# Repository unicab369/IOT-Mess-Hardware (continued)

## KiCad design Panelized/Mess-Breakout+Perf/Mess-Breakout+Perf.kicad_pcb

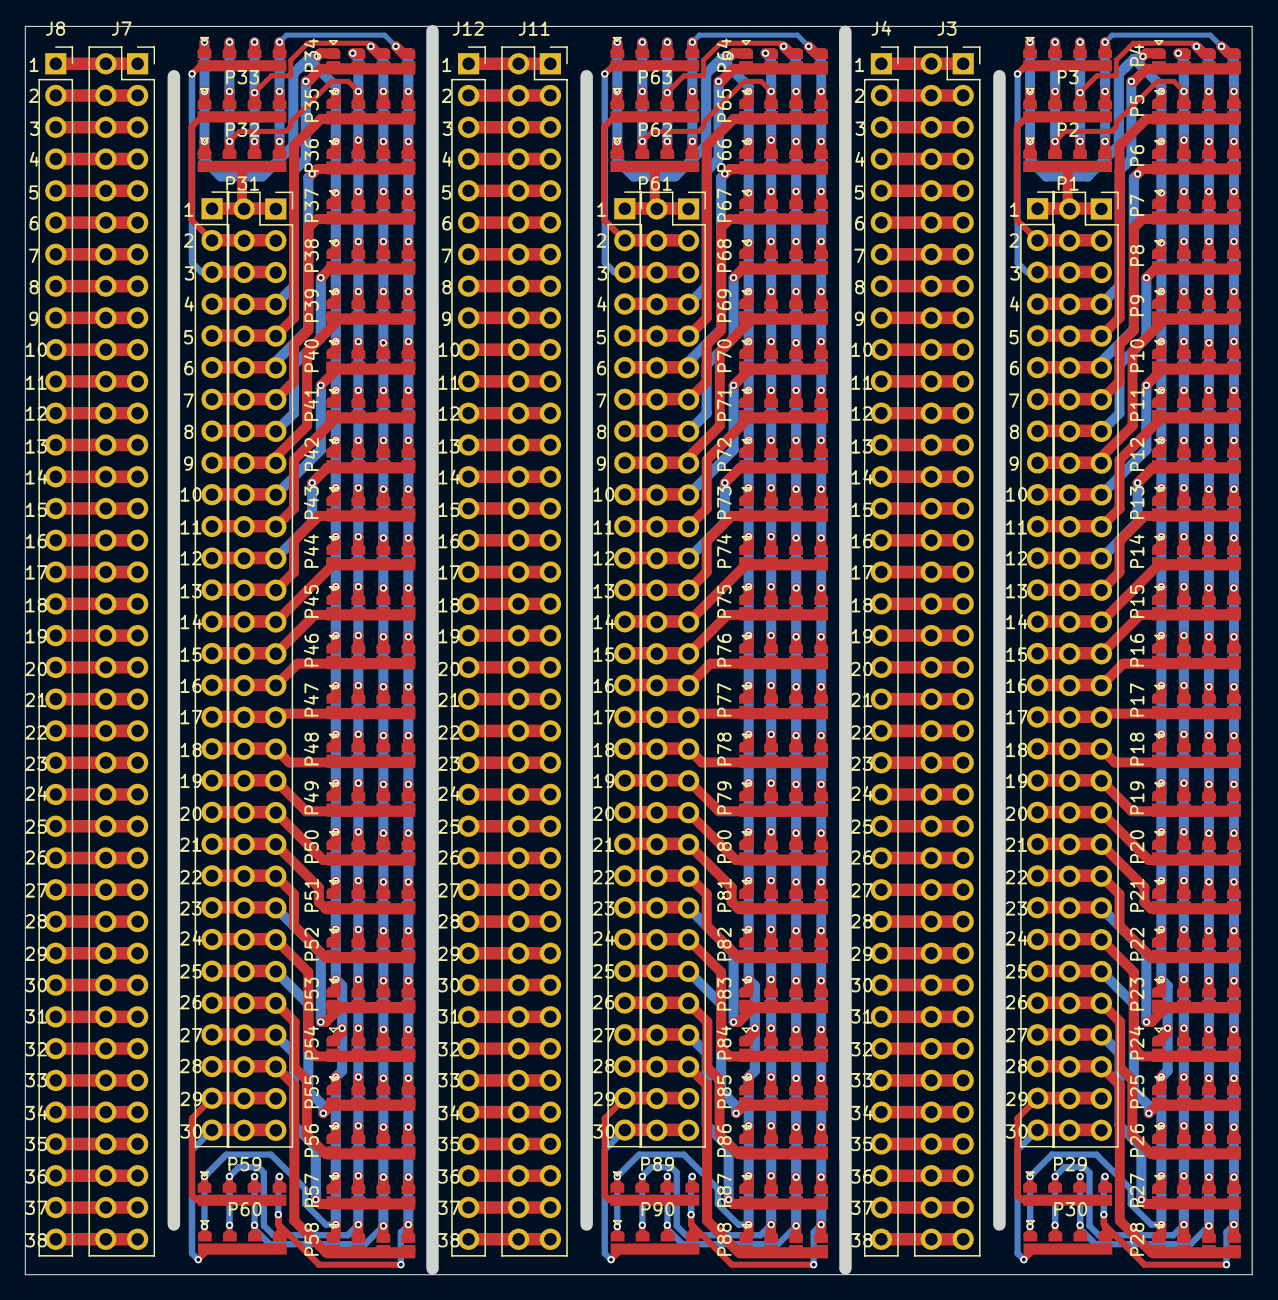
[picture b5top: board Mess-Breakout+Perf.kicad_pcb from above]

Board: 2 copper layers, 98.1 x 99.8 mm, 102 parts (0 on the bottom side), 72 nets.

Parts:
J2, J6, J10: Conn_01x30_Pin; PinSocket_1x30_P2.54mm_Vertical
J3, J7, J11: Conn_02x38_Odd_Even; PinSocket_2x38_P2.54mm_Vertical
J4, J8, J12: Conn_01x38_Pin; PinSocket_1x38_P2.54mm_Vertical
J5, J9, J13: Conn_02x30_Odd_Even; PinSocket_2x30_P2.54mm_Vertical
P1, P2, P3, P4, P5, P6, P7, P8, P9, P10, P11, P12, P13, P14, P15, P16, P17, P18, P19, P20, P21, P22, P23, P24, P25, P26, P27, P28, P29, P30, P31, P32, P33, P34, P35, P36, P37, P38, P39, P40, P41, P42, P43, P44, P45, P46, P47, P48, P49, P50, P51, P52, P53, P54, P55, P56, P57, P58, P59, P60, P61, P62, P63, P64, P65, P66, P67, P68, P69, P70, P71, P72, P73, P74, P75, P76, P77, P78, P79, P80, P81, P82, P83, P84, P85, P86, P87, P88, P89, P90: Jumper4x1

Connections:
/B1: J3.1, J3.2, J4.1, J7.1, J7.2, J8.1, J11.1, J11.2, J12.1
/B2: J3.3, J3.4, J4.2, J7.3, J7.4, J8.2, J11.3, J11.4, J12.2
/B3: J3.5, J3.6, J4.3, J7.5, J7.6, J8.3, J11.5, J11.6, J12.3
/B4: J3.7, J3.8, J4.4, J7.7, J7.8, J8.4, J11.7, J11.8, J12.4
/B5: J3.9, J3.10, J4.5, J7.9, J7.10, J8.5, J11.9, J11.10, J12.5
/B6: J3.11, J3.12, J4.6, J7.11, J7.12, J8.6, J11.11, J11.12, J12.6
/B7: J3.13, J3.14, J4.7, J7.13, J7.14, J8.7, J11.13, J11.14, J12.7
/B8: J3.15, J3.16, J4.8, J7.15, J7.16, J8.8, J11.15, J11.16, J12.8
/B9: J3.17, J3.18, J4.9, J7.17, J7.18, J8.9, J11.17, J11.18, J12.9
/B10: J3.19, J3.20, J4.10, J7.19, J7.20, J8.10, J11.19, J11.20, J12.10
/B11: J3.21, J3.22, J4.11, J7.21, J7.22, J8.11, J11.21, J11.22, J12.11
/B12: J3.23, J3.24, J4.12, J7.23, J7.24, J8.12, J11.23, J11.24, J12.12
/B13: J3.25, J3.26, J4.13, J7.25, J7.26, J8.13, J11.25, J11.26, J12.13
/B14: J3.27, J3.28, J4.14, J7.27, J7.28, J8.14, J11.27, J11.28, J12.14
/B15: J3.29, J3.30, J4.15, J7.29, J7.30, J8.15, J11.29, J11.30, J12.15
/B16: J3.31, J3.32, J4.16, J7.31, J7.32, J8.16, J11.31, J11.32, J12.16
/B17: J3.33, J3.34, J4.17, J7.33, J7.34, J8.17, J11.33, J11.34, J12.17
/B18: J3.35, J3.36, J4.18, J7.35, J7.36, J8.18, J11.35, J11.36, J12.18
/B19: J3.37, J3.38, J4.19, J7.37, J7.38, J8.19, J11.37, J11.38, J12.19
/B20: J3.39, J3.40, J4.20, J7.39, J7.40, J8.20, J11.39, J11.40, J12.20
/B21: J3.41, J3.42, J4.21, J7.41, J7.42, J8.21, J11.41, J11.42, J12.21
/B22: J3.43, J3.44, J4.22, J7.43, J7.44, J8.22, J11.43, J11.44, J12.22
/B23: J3.45, J3.46, J4.23, J7.45, J7.46, J8.23, J11.45, J11.46, J12.23
/B24: J3.47, J3.48, J4.24, J7.47, J7.48, J8.24, J11.47, J11.48, J12.24
/B25: J3.49, J3.50, J4.25, J7.49, J7.50, J8.25, J11.49, J11.50, J12.25
/B26: J3.51, J3.52, J4.26, J7.51, J7.52, J8.26, J11.51, J11.52, J12.26
/B27: J3.53, J3.54, J4.27, J7.53, J7.54, J8.27, J11.53, J11.54, J12.27
/B28: J3.55, J3.56, J4.28, J7.55, J7.56, J8.28, J11.55, J11.56, J12.28
/B29: J3.57, J3.58, J4.29, J7.57, J7.58, J8.29, J11.57, J11.58, J12.29
/B30: J3.59, J3.60, J4.30, J7.59, J7.60, J8.30, J11.59, J11.60, J12.30
/B31: J3.61, J3.62, J4.31, J7.61, J7.62, J8.31, J11.61, J11.62, J12.31
/B32: J3.63, J3.64, J4.32, J7.63, J7.64, J8.32, J11.63, J11.64, J12.32
/B33: J3.65, J3.66, J4.33, J7.65, J7.66, J8.33, J11.65, J11.66, J12.33
/B34: J3.67, J3.68, J4.34, J7.67, J7.68, J8.34, J11.67, J11.68, J12.34
/B35: J3.69, J3.70, J4.35, J7.69, J7.70, J8.35, J11.69, J11.70, J12.35
/B36: J3.71, J3.72, J4.36, J7.71, J7.72, J8.36, J11.71, J11.72, J12.36
/B37: J3.73, J3.74, J4.37, J7.73, J7.74, J8.37, J11.73, J11.74, J12.37
/B38: J3.75, J3.76, J4.38, J7.75, J7.76, J8.38, J11.75, J11.76, J12.38
/JA1: P1.1 (B), P2.1 (B), P3.1 (B), P4.1 (B), P5.1 (B), P6.1 (B), P7.1 (B), P8.1 (B), P9.1 (B), P10.1 (B), P11.1 (B), P12.1 (B), P13.1 (B), P14.1 (B), P15.1 (B), P16.1 (B), P17.1 (B), P18.1 (B), P19.1 (B), P20.1 (B), P21.1 (B), P22.1 (B), P23.1 (B), P24.1 (B), P25.1 (B), P26.1 (B), P27.1 (B), P28.1 (B), P29.1 (B), P30.1 (B), P31.1 (B), P32.1 (B), P33.1 (B), P34.1 (B), P35.1 (B), P36.1 (B), P37.1 (B), P38.1 (B), P39.1 (B), P40.1 (B), P41.1 (B), P42.1 (B), P43.1 (B), P44.1 (B), P45.1 (B), P46.1 (B), P47.1 (B), P48.1 (B), P49.1 (B), P50.1 (B), P51.1 (B), P52.1 (B), P53.1 (B), P54.1 (B), P55.1 (B), P56.1 (B), P57.1 (B), P58.1 (B), P59.1 (B), P60.1 (B), P61.1 (B), P62.1 (B), P63.1 (B), P64.1 (B), P65.1 (B), P66.1 (B), P67.1 (B), P68.1 (B), P69.1 (B), P70.1 (B), P71.1 (B), P72.1 (B), P73.1 (B), P74.1 (B), P75.1 (B), P76.1 (B), P77.1 (B), P78.1 (B), P79.1 (B), P80.1 (B), P81.1 (B), P82.1 (B), P83.1 (B), P84.1 (B), P85.1 (B), P86.1 (B), P87.1 (B), P88.1 (B), P89.1 (B), P90.1 (B)
/JA2: P1.2 (B), P2.2 (B), P3.2 (B), P4.2 (B), P5.2 (B), P6.2 (B), P7.2 (B), P8.2 (B), P9.2 (B), P10.2 (B), P11.2 (B), P12.2 (B), P13.2 (B), P14.2 (B), P15.2 (B), P16.2 (B), P17.2 (B), P18.2 (B), P19.2 (B), P20.2 (B), P21.2 (B), P22.2 (B), P23.2 (B), P24.2 (B), P25.2 (B), P26.2 (B), P27.2 (B), P28.2 (B), P29.2 (B), P30.2 (B), P31.2 (B), P32.2 (B), P33.2 (B), P34.2 (B), P35.2 (B), P36.2 (B), P37.2 (B), P38.2 (B), P39.2 (B), P40.2 (B), P41.2 (B), P42.2 (B), P43.2 (B), P44.2 (B), P45.2 (B), P46.2 (B), P47.2 (B), P48.2 (B), P49.2 (B), P50.2 (B), P51.2 (B), P52.2 (B), P53.2 (B), P54.2 (B), P55.2 (B), P56.2 (B), P57.2 (B), P58.2 (B), P59.2 (B), P60.2 (B), P61.2 (B), P62.2 (B), P63.2 (B), P64.2 (B), P65.2 (B), P66.2 (B), P67.2 (B), P68.2 (B), P69.2 (B), P70.2 (B), P71.2 (B), P72.2 (B), P73.2 (B), P74.2 (B), P75.2 (B), P76.2 (B), P77.2 (B), P78.2 (B), P79.2 (B), P80.2 (B), P81.2 (B), P82.2 (B), P83.2 (B), P84.2 (B), P85.2 (B), P86.2 (B), P87.2 (B), P88.2 (B), P89.2 (B), P90.2 (B)
/JA3: P1.3 (B), P2.3 (B), P3.3 (B), P4.3 (B), P5.3 (B), P6.3 (B), P7.3 (B), P8.3 (B), P9.3 (B), P10.3 (B), P11.3 (B), P12.3 (B), P13.3 (B), P14.3 (B), P15.3 (B), P16.3 (B), P17.3 (B), P18.3 (B), P19.3 (B), P20.3 (B), P21.3 (B), P22.3 (B), P23.3 (B), P24.3 (B), P25.3 (B), P26.3 (B), P27.3 (B), P28.3 (B), P29.3 (B), P30.3 (B), P31.3 (B), P32.3 (B), P33.3 (B), P34.3 (B), P35.3 (B), P36.3 (B), P37.3 (B), P38.3 (B), P39.3 (B), P40.3 (B), P41.3 (B), P42.3 (B), P43.3 (B), P44.3 (B), P45.3 (B), P46.3 (B), P47.3 (B), P48.3 (B), P49.3 (B), P50.3 (B), P51.3 (B), P52.3 (B), P53.3 (B), P54.3 (B), P55.3 (B), P56.3 (B), P57.3 (B), P58.3 (B), P59.3 (B), P60.3 (B), P61.3 (B), P62.3 (B), P63.3 (B), P64.3 (B), P65.3 (B), P66.3 (B), P67.3 (B), P68.3 (B), P69.3 (B), P70.3 (B), P71.3 (B), P72.3 (B), P73.3 (B), P74.3 (B), P75.3 (B), P76.3 (B), P77.3 (B), P78.3 (B), P79.3 (B), P80.3 (B), P81.3 (B), P82.3 (B), P83.3 (B), P84.3 (B), P85.3 (B), P86.3 (B), P87.3 (B), P88.3 (B), P89.3 (B), P90.3 (B)
/JA4: P1.4 (B), P2.4 (B), P3.4 (B), P4.4 (B), P5.4 (B), P6.4 (B), P7.4 (B), P8.4 (B), P9.4 (B), P10.4 (B), P11.4 (B), P12.4 (B), P13.4 (B), P14.4 (B), P15.4 (B), P16.4 (B), P17.4 (B), P18.4 (B), P19.4 (B), P20.4 (B), P21.4 (B), P22.4 (B), P23.4 (B), P24.4 (B), P25.4 (B), P26.4 (B), P27.4 (B), P28.4 (B), P29.4 (B), P30.4 (B), P31.4 (B), P32.4 (B), P33.4 (B), P34.4 (B), P35.4 (B), P36.4 (B), P37.4 (B), P38.4 (B), P39.4 (B), P40.4 (B), P41.4 (B), P42.4 (B), P43.4 (B), P44.4 (B), P45.4 (B), P46.4 (B), P47.4 (B), P48.4 (B), P49.4 (B), P50.4 (B), P51.4 (B), P52.4 (B), P53.4 (B), P54.4 (B), P55.4 (B), P56.4 (B), P57.4 (B), P58.4 (B), P59.4 (B), P60.4 (B), P61.4 (B), P62.4 (B), P63.4 (B), P64.4 (B), P65.4 (B), P66.4 (B), P67.4 (B), P68.4 (B), P69.4 (B), P70.4 (B), P71.4 (B), P72.4 (B), P73.4 (B), P74.4 (B), P75.4 (B), P76.4 (B), P77.4 (B), P78.4 (B), P79.4 (B), P80.4 (B), P81.4 (B), P82.4 (B), P83.4 (B), P84.4 (B), P85.4 (B), P86.4 (B), P87.4 (B), P88.4 (B), P89.4 (B), P90.4 (B)
P1: J2.1, J5.1, J5.2, J6.1, J9.1, J9.2, J10.1, J13.1, J13.2, P1.0 (C), P31.0 (C), P61.0 (C)
P2: J2.2, J5.3, J5.4, J6.2, J9.3, J9.4, J10.2, J13.3, J13.4, P2.0 (C), P32.0 (C), P62.0 (C)
P3: J2.3, J5.5, J5.6, J6.3, J9.5, J9.6, J10.3, J13.5, J13.6, P3.0 (C), P33.0 (C), P63.0 (C)
P4: J2.4, J5.7, J5.8, J6.4, J9.7, J9.8, J10.4, J13.7, J13.8, P4.0 (C), P34.0 (C), P64.0 (C)
P5: J2.5, J5.9, J5.10, J6.5, J9.9, J9.10, J10.5, J13.9, J13.10, P5.0 (C), P35.0 (C), P65.0 (C)
P6: J2.6, J5.11, J5.12, J6.6, J9.11, J9.12, J10.6, J13.11, J13.12, P6.0 (C), P36.0 (C), P66.0 (C)
P7: J2.7, J5.13, J5.14, J6.7, J9.13, J9.14, J10.7, J13.13, J13.14, P7.0 (C), P37.0 (C), P67.0 (C)
P8: J2.8, J5.15, J5.16, J6.8, J9.15, J9.16, J10.8, J13.15, J13.16, P8.0 (C), P38.0 (C), P68.0 (C)
P9: J2.9, J5.17, J5.18, J6.9, J9.17, J9.18, J10.9, J13.17, J13.18, P9.0 (C), P39.0 (C), P69.0 (C)
P10: J2.10, J5.19, J5.20, J6.10, J9.19, J9.20, J10.10, J13.19, J13.20, P10.0 (C), P40.0 (C), P70.0 (C)
P11: J2.11, J5.21, J5.22, J6.11, J9.21, J9.22, J10.11, J13.21, J13.22, P11.0 (C), P41.0 (C), P71.0 (C)
P12: J2.12, J5.23, J5.24, J6.12, J9.23, J9.24, J10.12, J13.23, J13.24, P12.0 (C), P42.0 (C), P72.0 (C)
P13: J2.13, J5.25, J5.26, J6.13, J9.25, J9.26, J10.13, J13.25, J13.26, P13.0 (C), P43.0 (C), P73.0 (C)
P14: J2.14, J5.27, J5.28, J6.14, J9.27, J9.28, J10.14, J13.27, J13.28, P14.0 (C), P44.0 (C), P74.0 (C)
P15: J2.15, J5.29, J5.30, J6.15, J9.29, J9.30, J10.15, J13.29, J13.30, P15.0 (C), P45.0 (C), P75.0 (C)
P16: J2.16, J5.31, J5.32, J6.16, J9.31, J9.32, J10.16, J13.31, J13.32, P16.0 (C), P46.0 (C), P76.0 (C)
P17: J2.17, J5.33, J5.34, J6.17, J9.33, J9.34, J10.17, J13.33, J13.34, P17.0 (C), P47.0 (C), P77.0 (C)
P18: J2.18, J5.35, J5.36, J6.18, J9.35, J9.36, J10.18, J13.35, J13.36, P18.0 (C), P48.0 (C), P78.0 (C)
P19: J2.19, J5.37, J5.38, J6.19, J9.37, J9.38, J10.19, J13.37, J13.38, P19.0 (C), P49.0 (C), P79.0 (C)
P20: J2.20, J5.39, J5.40, J6.20, J9.39, J9.40, J10.20, J13.39, J13.40, P20.0 (C), P50.0 (C), P80.0 (C)
P21: J2.21, J5.41, J5.42, J6.21, J9.41, J9.42, J10.21, J13.41, J13.42, P21.0 (C), P51.0 (C), P81.0 (C)
P22: J2.22, J5.43, J5.44, J6.22, J9.43, J9.44, J10.22, J13.43, J13.44, P22.0 (C), P52.0 (C), P82.0 (C)
P23: J2.23, J5.45, J5.46, J6.23, J9.45, J9.46, J10.23, J13.45, J13.46, P23.0 (C), P53.0 (C), P83.0 (C)
P24: J2.24, J5.47, J5.48, J6.24, J9.47, J9.48, J10.24, J13.47, J13.48, P24.0 (C), P54.0 (C), P84.0 (C)
P25: J2.25, J5.49, J5.50, J6.25, J9.49, J9.50, J10.25, J13.49, J13.50, P25.0 (C), P55.0 (C), P85.0 (C)
P26: J2.26, J5.51, J5.52, J6.26, J9.51, J9.52, J10.26, J13.51, J13.52, P26.0 (C), P56.0 (C), P86.0 (C)
P27: J2.27, J5.53, J5.54, J6.27, J9.53, J9.54, J10.27, J13.53, J13.54, P27.0 (C), P57.0 (C), P87.0 (C)
P28: J2.28, J5.55, J5.56, J6.28, J9.55, J9.56, J10.28, J13.55, J13.56, P28.0 (C), P58.0 (C), P88.0 (C)
P29: J2.29, J5.57, J5.58, J6.29, J9.57, J9.58, J10.29, J13.57, J13.58, P29.0 (C), P59.0 (C), P89.0 (C)
P30: J2.30, J5.59, J5.60, J6.30, J9.59, J9.60, J10.30, J13.59, J13.60, P30.0 (C), P60.0 (C), P90.0 (C)

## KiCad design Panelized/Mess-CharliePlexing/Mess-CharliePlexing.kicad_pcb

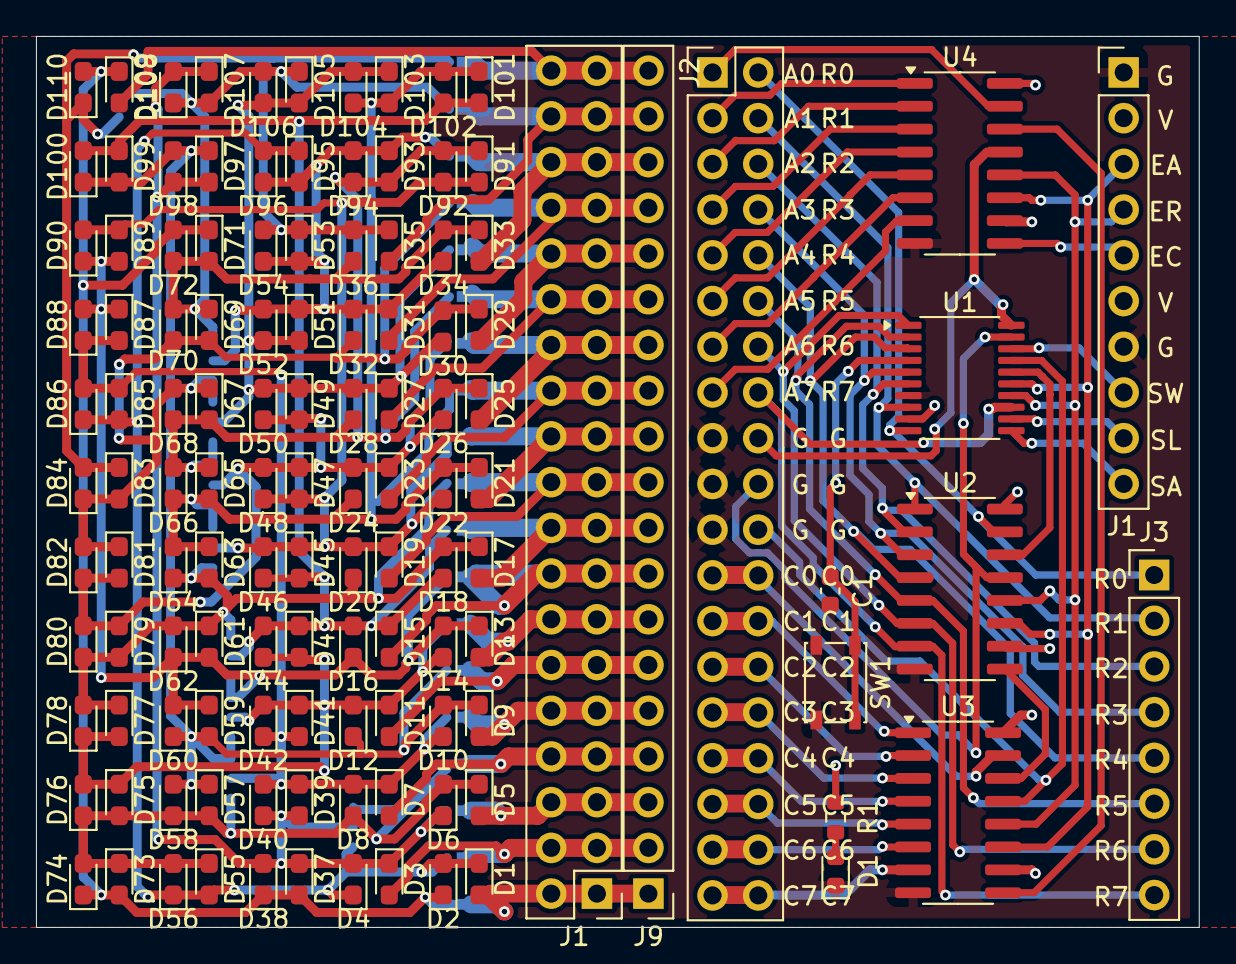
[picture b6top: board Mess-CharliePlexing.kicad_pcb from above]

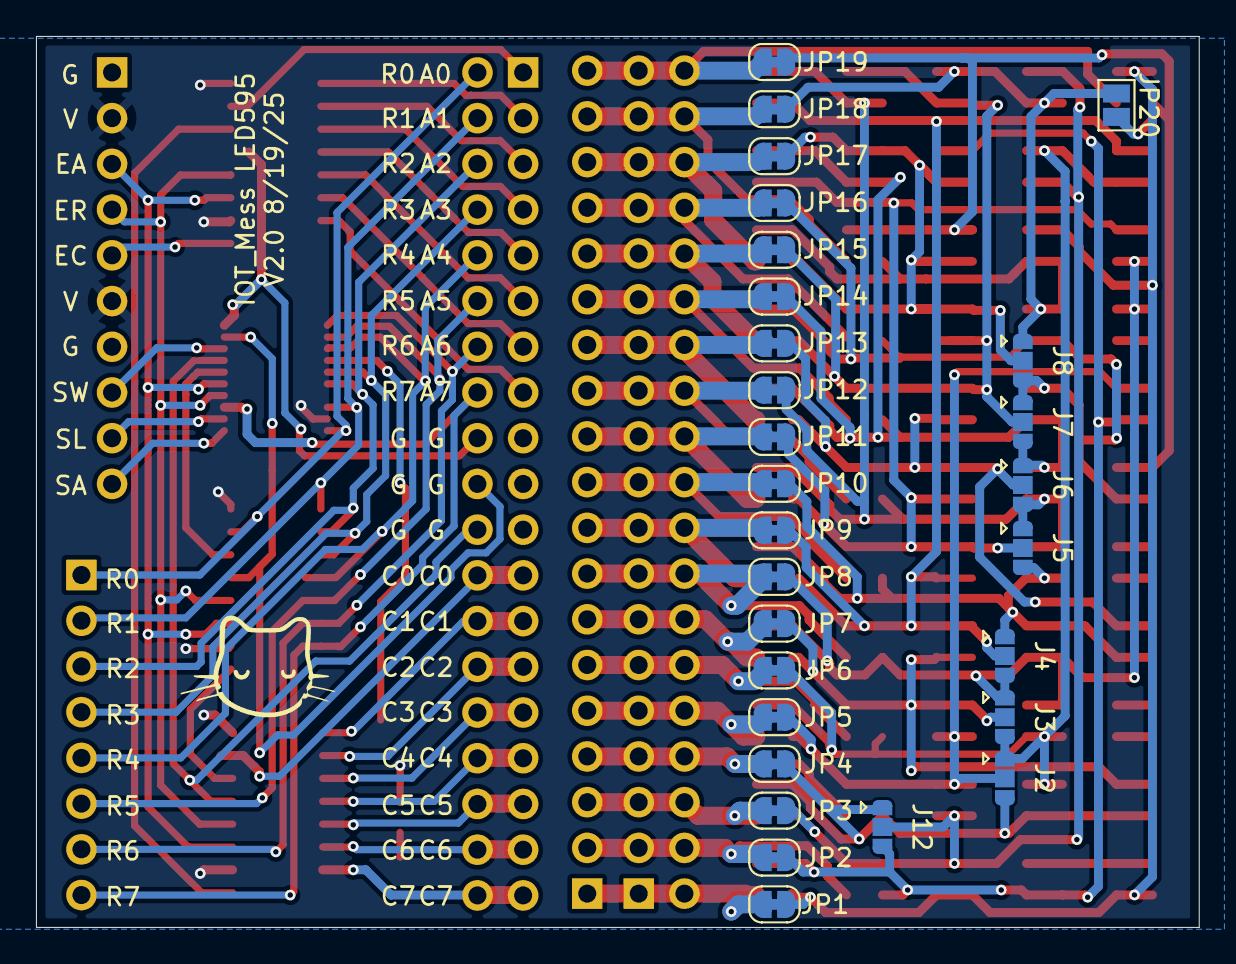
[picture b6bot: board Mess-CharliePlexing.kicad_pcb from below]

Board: 2 copper layers, 64.6 x 49.5 mm, 151 parts (28 on the bottom side), 78 nets.

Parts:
C1: .1u; C_0603_1608Metric
D1: LED; LED_0603_1608Metric
D1#2, D2, D3, D4, D5, D6, D7, D8, D9, D10, D11, D12, D13, D14, D15, D16, D17, D18, D19, D20, D21, D22, D23, D24, D25, D26, D27, D28, D29, D30, D31, D32, D33, D34, D35, D36, D37, D38, D39, D40, D41, D42, D43, D44, D45, D46, D47, D48, D49, D50, D51, D52, D53, D54, D55, D56, D57, D58, D59, D60, D61, D62, D63, D64, D65, D66, D67, D68, D69, D70, D71, D72, D73, D74, D75, D76, D77, D78, D79, D80, D81, D82, D83, D84, D85, D86, D87, D88, D89, D90, D91, D92, D93, D94, D95, D96, D97, D98, D99, D100, D101, D102, D103, D104, D105, D106, D107, D108, D109, D110: LED; LED_0603_1608Metric_Pad1.05x0.95mm_HandSolder
J1, J2: Conn_02x19_Odd_Even; PinHeader_2x19_P2.54mm_Vertical
J1#2: Conn_01x10_Pin; PinHeader_1x10_P2.54mm_Vertical
J2#2, J3#2, J4, J5, J6, J7, J8, J12: Jumper; Jumper-3_P1.3mm_Open_RoundedPad1.0x1.5mm
J3: Conn_01x08_Pin; PinHeader_1x08_P2.54mm_Vertical
J9: Conn_01x19_Pin; PinHeader_1x19_P2.54mm_Vertical
JP1, JP2, JP3, JP4, JP5, JP6, JP7, JP8, JP9, JP10, JP11, JP12, JP13, JP14, JP15, JP16, JP17, JP18, JP19: Jumper; SolderJumper-2_P1.3mm_Bridged_RoundedPad1.0x1.5mm
JP20: Jumper_2_Open; SolderJumper-2_P1.3mm_Open_Pad1.0x1.5mm
R1: R; R_0603_1608Metric
SW1: SW_Push; SW_SPST_PTS810
U1: TSSOP-20_4.4x6.5mm_P0.65mm
U2, U3, U4: 74HC595; SOP-16_3.9x9.9mm_P1.27mm

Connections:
/P2: D1#2.2 (A), J1.1, J1.2, J9.1, JP1.1 (A)
/P4: D3.2 (A), J1.3, J1.4, J9.2, JP2.1 (A)
/P6: D5.2 (A), J1.5, J1.6, J9.3, JP3.1 (A)
/P8: D7.2 (A), J1.7, J1.8, J9.4, JP4.1 (A)
/P10: D9.2 (A), J1.9, J1.10, J9.5, JP5.1 (A)
/P12: D11.2 (A), J1.11, J1.12, J9.6, JP6.1 (A)
/P14: D13.2 (A), J1.13, J1.14, J9.7, JP7.1 (A)
/P16: D15.2 (A), J1.15, J1.16, J9.8, JP8.1 (A)
/P18: D17.2 (A), J1.17, J1.18, J9.9, JP9.1 (A)
/P20: D19.2 (A), J1.19, J1.20, J9.10, JP10.1 (A)
/P22: D21.2 (A), J1.21, J1.22, J9.11, JP11.1 (A)
/P24: D23.2 (A), J1.23, J1.24, J9.12, JP12.1 (A)
/P26: D25.2 (A), J1.25, J1.26, J9.13, JP13.1 (A)
/P28: D27.2 (A), J1.27, J1.28, J9.14, JP14.1 (A)
/P30: D29.2 (A), J1.29, J1.30, J9.15, JP15.1 (A)
/P32: D31.2 (A), J1.31, J1.32, J9.16, JP16.1 (A)
/P34: D33.2 (A), J1.33, J1.34, J9.17, JP17.1 (A)
/P36: D35.2 (A), J1.35, J1.36, J9.18, JP18.1 (A)
/P38: D109.2 (A), J1.37, J1.38, J9.19, JP19.1 (A)
A_0: J2.1, U4.15 (QA)
A_1: J2.3, U4.1 (QB)
A_2: J2.5, U4.2 (QC)
A_3: J2.7, U4.3 (QD)
A_4: J2.9, U4.4 (QE)
A_5: J2.11, U4.5 (QF)
A_6: J2.13, U4.6 (QG)
A_7: J2.15, U4.7 (QH)
C0: J2.23, J2.24, U3.15 (QA)
C1: J2.25, J2.26, U3.1 (QB)
C2: J2.27, J2.28, U3.2 (QC)
C3: J2.29, J2.30, U3.3 (QD)
C4: J2.31, J2.32, U3.4 (QE)
C5: J2.33, J2.34, U3.5 (QF)
C6: J2.35, J2.36, U3.6 (QG)
C7: J2.37, J2.38, U3.7 (QH)
CLCK: J1#2.3, U1.15 (PC5/VSS*), U2.11 (SRCLK), U3.11 (SRCLK), U4.11 (SRCLK)
DATA: U1.16 (PC6/MOSI/VDD*), U2.14 (SER)
EN_A: J2.18, U1.20 (PD3/A4/ANT*), U4.13 (~OE)
EN_C: J2.22, U1.17 (PC7/MISO/UDM*), U3.13 (~OE)
EN_R: J2.20, U1.19 (PD2/A3/SWIO*), U2.13 (~OE)
GND: C1.2, D1.1 (K), J1#2.1, J1#2.7, J2.17, J2.19, J2.21, SW1.1, U1.7 (VSS), U2.8 (GND), U3.8 (GND), U4.8 (GND)
LATCH: J1#2.4, U1.14 (PC4/A2), U2.12 (RCLK), U3.12 (RCLK), U4.12 (RCLK)
unnamed: D1.2 (A), R1.2
unnamed: D1#2.1 (K), D2.2 (A), D4.1 (K), D55.2 (A), D56.1 (K), D85.2 (A), D86.1 (K), D95.1 (K), D96.2 (A), J12.3 (B), JP2.2 (B)
unnamed: D5.1 (K), D6.2 (A), D8.1 (K), D55.1 (K), D56.2 (A), D57.2 (A), D58.1 (K), D73.1 (K), D74.2 (A), D75.2 (A), D76.1 (K), J2#2.3 (B), J12.1 (A), JP4.2 (B)
unnamed: D9.1 (K), D10.2 (A), D12.1 (K), D57.1 (K), D58.2 (A), D59.2 (A), D60.1 (K), D97.1 (K), D98.2 (A), D99.2 (A), D100.1 (K), J2#2.1 (A), J3#2.3 (B), JP6.2 (B)
unnamed: D7.1 (K), D8.2 (A), D10.1 (K), D39.1 (K), D40.2 (A), D41.2 (A), D42.1 (K), D85.1 (K), D86.2 (A), D87.2 (A), D88.1 (K), J2#2.2 (C), JP5.2 (B)
unnamed: D11.1 (K), D12.2 (A), D14.1 (K), D41.1 (K), D42.2 (A), D43.2 (A), D44.1 (K), D75.1 (K), D76.2 (A), D77.2 (A), D78.1 (K), J3#2.2 (C), JP7.2 (B)
unnamed: D13.1 (K), D14.2 (A), D16.1 (K), D59.1 (K), D60.2 (A), D61.2 (A), D62.1 (K), D87.1 (K), D88.2 (A), D89.2 (A), D90.1 (K), J3#2.1 (A), J4.3 (B), JP8.2 (B)
unnamed: D17.1 (K), D18.2 (A), D20.1 (K), D61.1 (K), D62.2 (A), D63.2 (A), D64.1 (K), D77.1 (K), D78.2 (A), D79.2 (A), D80.1 (K), J4.1 (A), J5.3 (B), JP10.2 (B)
unnamed: D19.1 (K), D20.2 (A), D22.1 (K), D45.1 (K), D46.2 (A), D47.2 (A), D48.1 (K), D89.1 (K), D90.2 (A), D91.2 (A), D92.1 (K), J5.2 (C), JP11.2 (B)
unnamed: D23.1 (K), D24.2 (A), D26.1 (K), D47.1 (K), D48.2 (A), D49.2 (A), D50.1 (K), D79.1 (K), D80.2 (A), D81.2 (A), D82.1 (K), J6.2 (C), JP13.2 (B)
unnamed: D25.1 (K), D26.2 (A), D28.1 (K), D65.1 (K), D66.2 (A), D67.2 (A), D68.1 (K), D91.1 (K), D92.2 (A), D93.2 (A), D94.1 (K), J6.1 (A), J7.3 (B), JP14.2 (B)
unnamed: D29.1 (K), D30.2 (A), D32.1 (K), D67.1 (K), D68.2 (A), D69.2 (A), D70.1 (K), D81.1 (K), D82.2 (A), D83.2 (A), D84.1 (K), J7.1 (A), J8.3 (B), JP16.2 (B)
unnamed: D31.1 (K), D32.2 (A), D34.1 (K), D51.1 (K), D52.2 (A), D53.2 (A), D54.1 (K), D93.1 (K), D94.2 (A), D95.2 (A), D96.1 (K), J8.2 (C), JP17.2 (B)
unnamed: D15.1 (K), D16.2 (A), D18.1 (K), D43.1 (K), D44.2 (A), D45.2 (A), D46.1 (K), D99.1 (K), D100.2 (A), D101.2 (A), D102.1 (K), J4.2 (C), JP9.2 (B)
unnamed: D21.1 (K), D22.2 (A), D24.1 (K), D63.1 (K), D64.2 (A), D65.2 (A), D66.1 (K), D101.1 (K), D102.2 (A), D103.2 (A), D104.1 (K), J5.1 (A), J6.3 (B), JP12.2 (B)
unnamed: D27.1 (K), D28.2 (A), D30.1 (K), D49.1 (K), D50.2 (A), D51.2 (A), D52.1 (K), D103.1 (K), D104.2 (A), D105.2 (A), D106.1 (K), J7.2 (C), JP15.2 (B)
unnamed: D33.1 (K), D34.2 (A), D36.1 (K), D69.1 (K), D70.2 (A), D71.2 (A), D72.1 (K), D105.1 (K), D106.2 (A), D107.2 (A), D108.1 (K), J8.1 (A), JP18.2 (B), JP20.1 (A)
unnamed: D3.1 (K), D4.2 (A), D6.1 (K), D37.1 (K), D38.2 (A), D39.2 (A), D40.1 (K), D97.2 (A), D98.1 (K), D107.1 (K), D108.2 (A), J12.2 (C), JP3.2 (B)
unnamed: D2.1 (K), D37.2 (A), D38.1 (K), D71.1 (K), D72.2 (A), D73.2 (A), D74.1 (K), D109.1 (K), D110.2 (A), JP1.2 (B)
unnamed: D35.1 (K), D36.2 (A), D53.1 (K), D54.2 (A), D83.1 (K), D84.2 (A), D110.1 (K), JP19.2 (B), JP20.2 (B)
unnamed: J1#2.5, U4.9 (QH')
unnamed: C1.1, SW1.2, U1.4 (PD7/RST)
unnamed: U2.9 (QH'), U3.14 (SER)
unnamed: U3.9 (QH'), U4.14 (SER)
R0: J2.2, J3.1, U1.10 (PC0), U2.15 (QA)
R1: J2.4, J3.2, U1.8 (PD0), U2.1 (QB)
R2: J2.6, J3.3, U1.6 (PA2/OSCO), U2.2 (QC)
R3: J2.8, J3.4, U1.5 (PA1/OSCI), U2.3 (QD)
R4: J2.10, J3.5, U1.3 (PD6/A6/OSCO*), U2.4 (QE)
R5: J2.12, J3.6, U1.2 (PD5/A5/OSCI*), U2.5 (QF)
R6: J2.14, J3.7, U1.1 (PD4/A7), U2.6 (QG)
R7: J2.16, J3.8, U1.13 (PC3), U2.7 (QH)
SCL: J1#2.9, U1.12 (PC2/SCL)
SDA: J1#2.10, U1.11 (PC1/SDA)
SWIO: J1#2.8, U1.18 (PD1/SWIO/UDP*)
VCC: J1#2.2, J1#2.6, R1.1, U1.9 (VDD), U2.10 (~SRCLR), U2.16 (VCC), U3.10 (~SRCLR), U3.16 (VCC), U4.10 (~SRCLR), U4.16 (VCC)
